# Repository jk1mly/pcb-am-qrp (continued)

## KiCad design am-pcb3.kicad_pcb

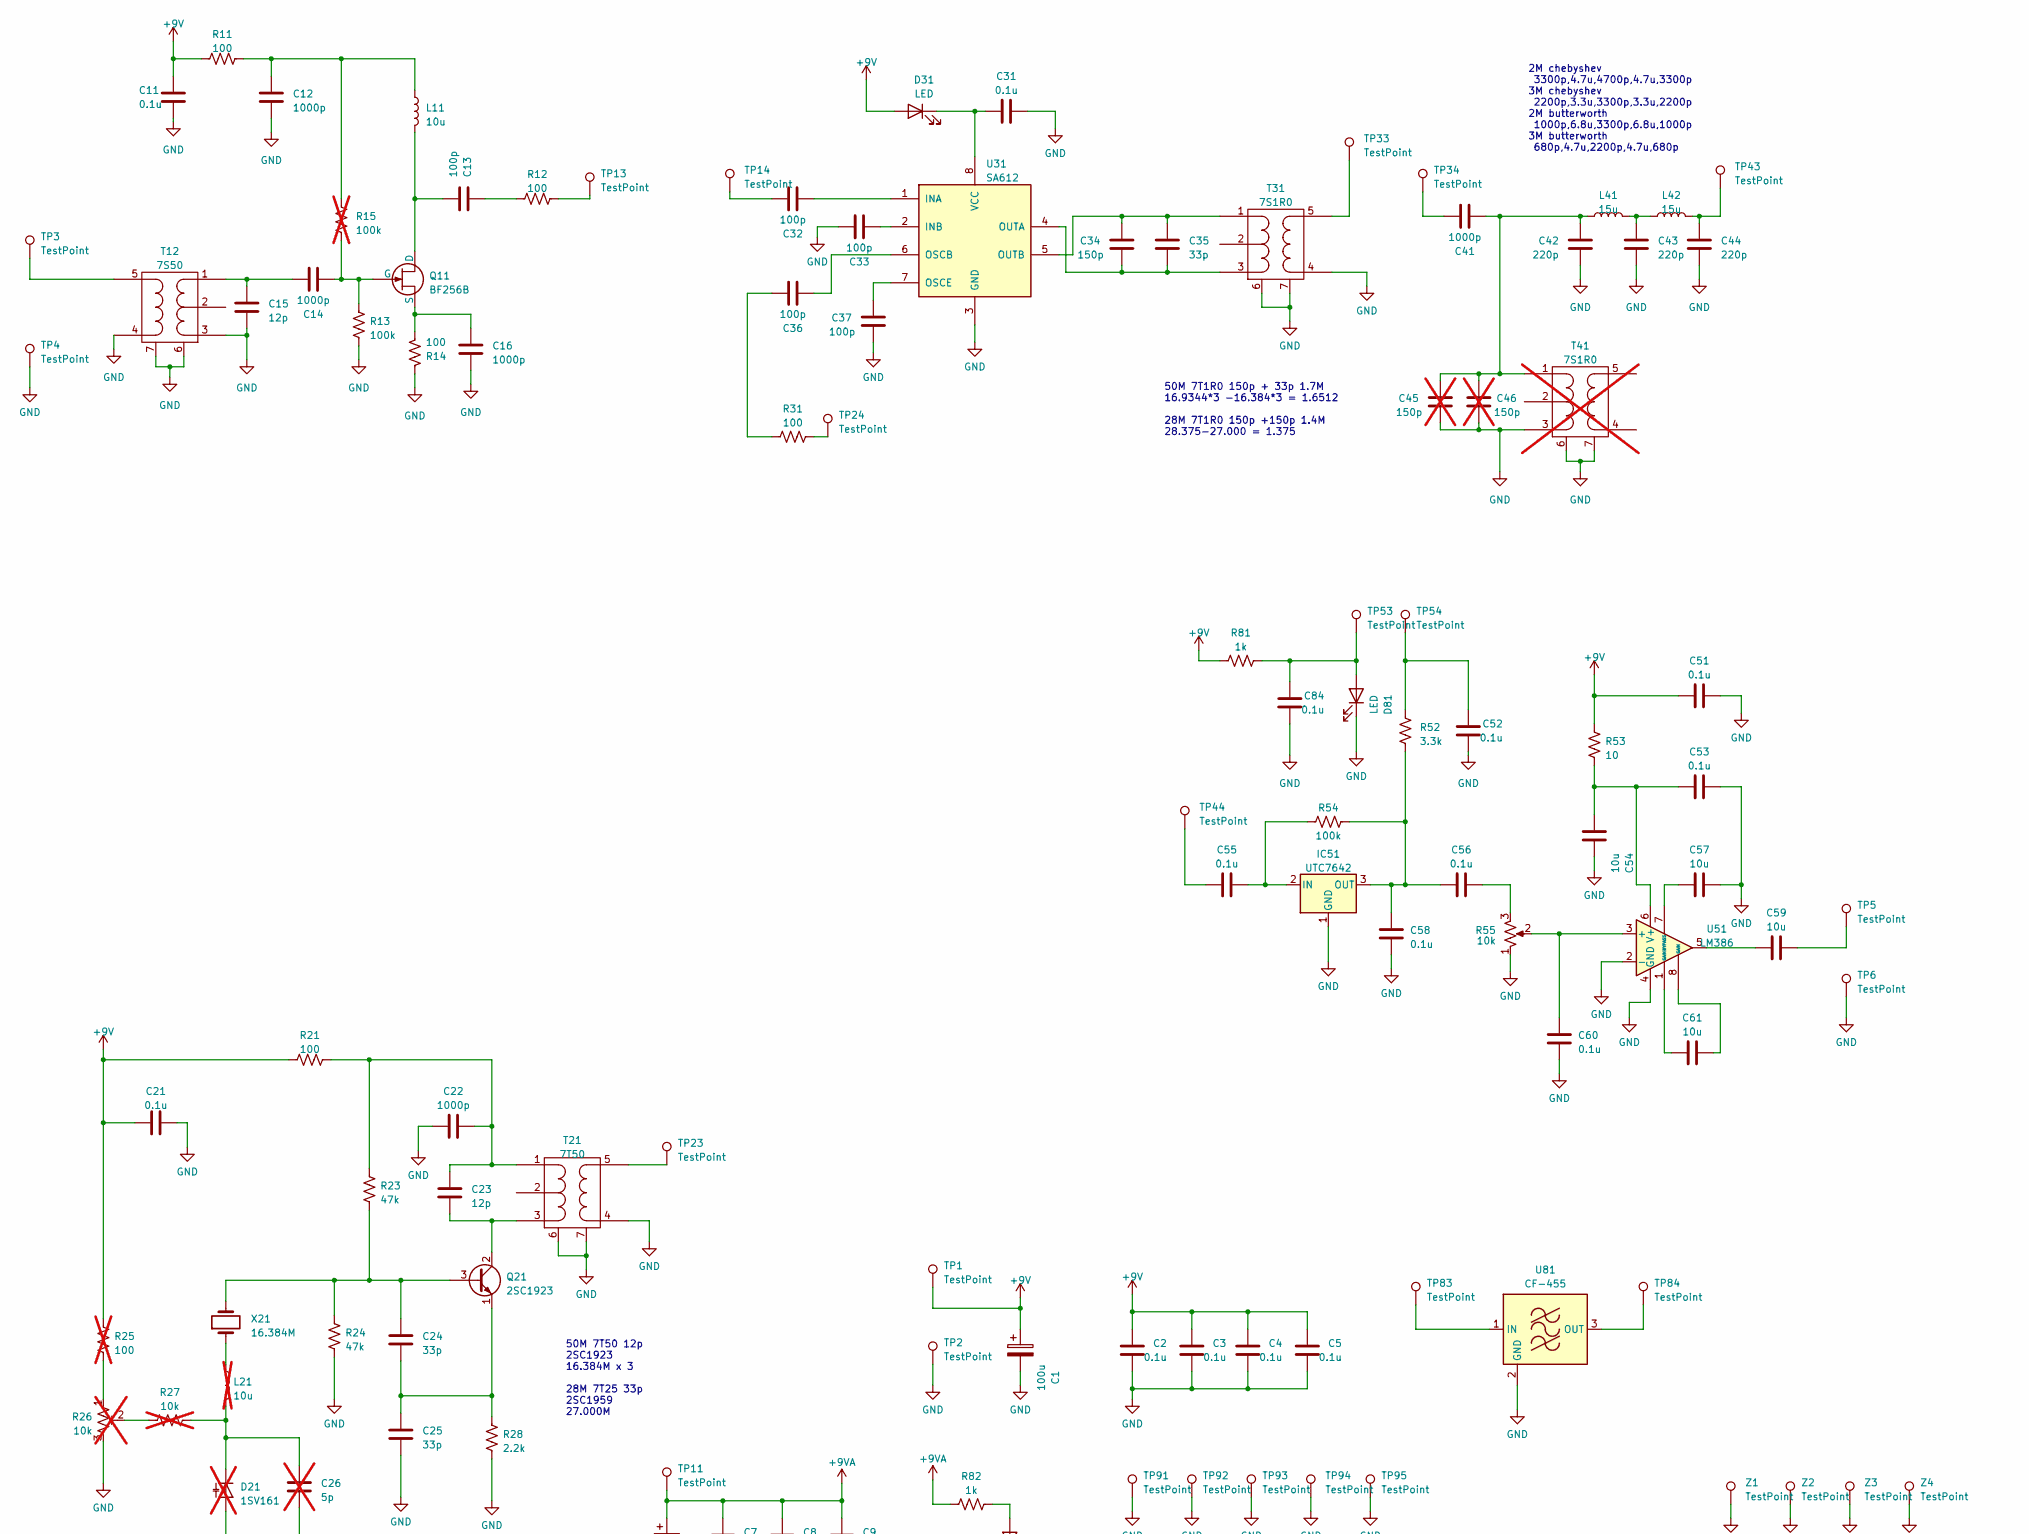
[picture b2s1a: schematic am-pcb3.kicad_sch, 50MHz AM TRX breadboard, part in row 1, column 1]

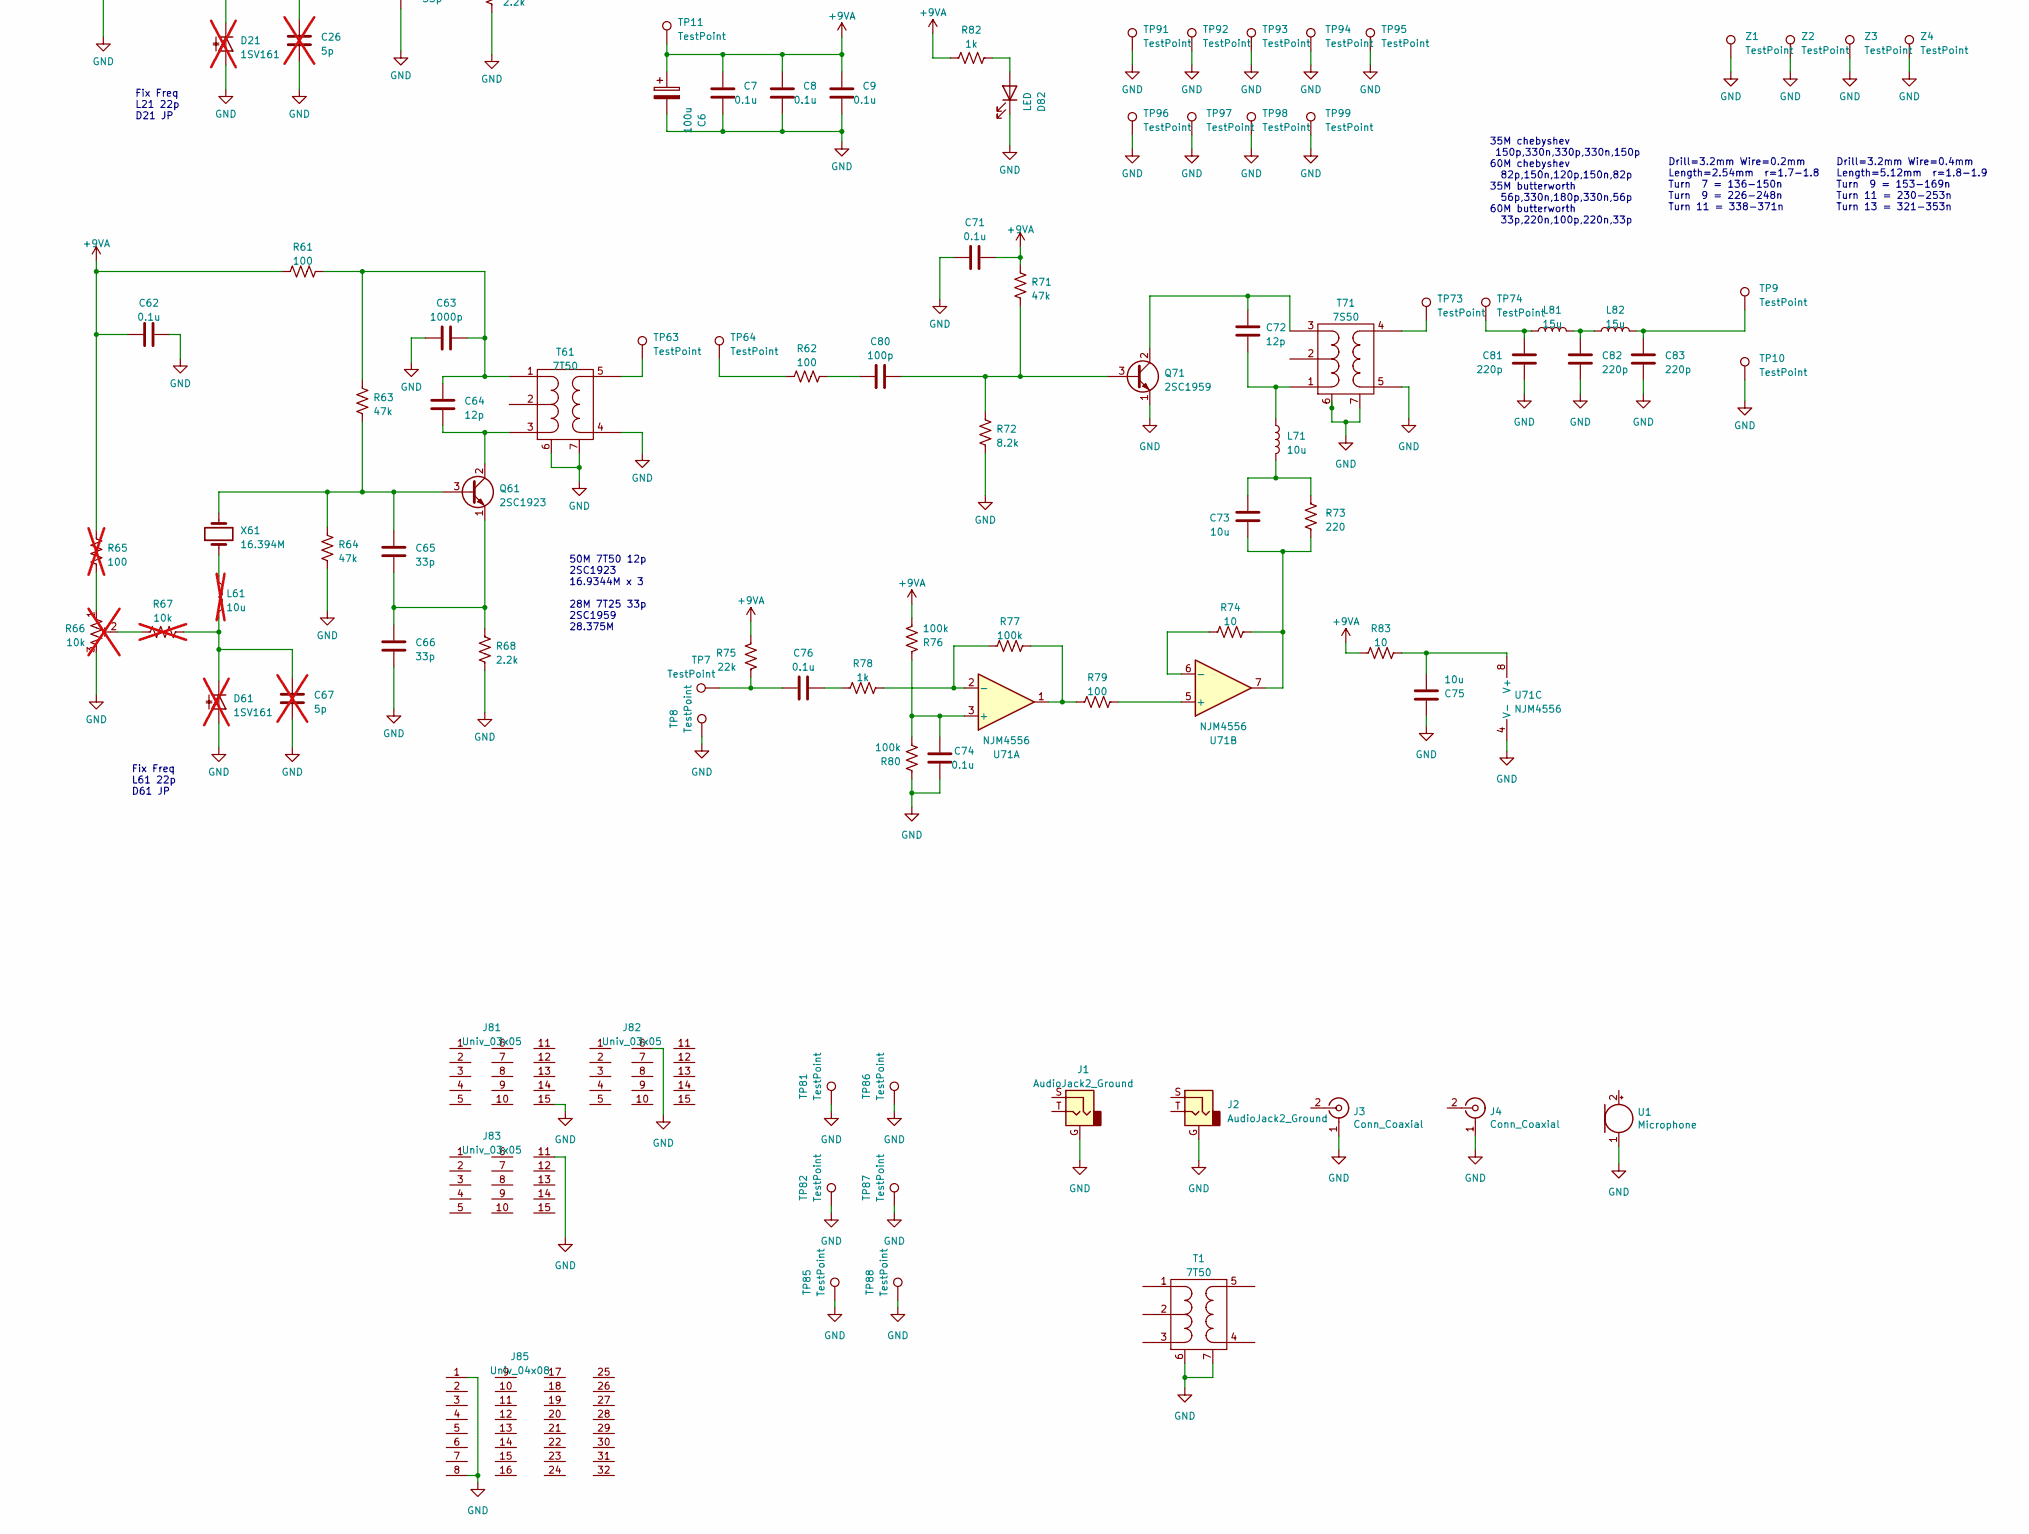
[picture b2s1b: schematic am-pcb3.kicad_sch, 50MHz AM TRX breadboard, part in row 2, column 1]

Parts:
C1, C6: 100u; CP_Radial_D7.5mm_P2.54mm_dot
C2, C3, C4, C5, C7, C8, C9, C11, C21, C31, C51, C52, C53, C55, C56, C58, C60, C62, C71, C74, C76, C84: 0.1u; C_Disc_P2.54mm
C12, C14, C16, C22, C41, C63: 1000p; C_Disc_P2.54mm
C13, C32, C33, C36, C37, C80: 100p; C_Disc_P2.54mm
C15, C23, C64, C72: 12p; C_Disc_P2.54mm
C24, C25, C35, C65, C66: 33p; C_Disc_P2.54mm
C26, C67: 5p; C_Disc_P2.54mm; not fitted
C34: 150p; C_Disc_P2.54mm
C42, C43, C44, C81, C82, C83: 220p; C_Disc_P2.54mm
C45, C46: 150p; C_Disc_P2.54mm; not fitted
C54, C57, C59, C61, C73, C75: 10u; C_Disc_P5.12mm
D21, D61: 1SV161; D_T-1_P5.08mm_Horizontal; not fitted
D31, D81, D82: LED; LED_D3.0mm
IC51: UTC7642; TO-92_Inline_Wide
J1, J2: AudioJack2_Ground; Jack_3.5mm_CUI_SJ1-3525N_Horizontal
J3, J4: Conn_Coaxial; RF_SMA_Vertical_5-1814832-1
J81, J82, J83: Univ_03x05; univ_03x05
J85: Univ_04x08; univ_04x08
L11, L71: 10u; R_Axial_DIN0207_L6.3mm_D2.2mm_P2.54mm_Vertical
L21, L61: 10u; R_Axial_DIN0207_L6.3mm_D2.2mm_P2.54mm_Vertical; not fitted
L41, L42, L81, L82: 15u; R_Axial_DIN0207_L6.3mm_D2.2mm_P2.54mm_Vertical
Q11: BF256B; TO-92_Inline_Wide
Q21, Q61: 2SC1923; TO-92_Inline_Wide
Q71: 2SC1959; TO-92_Inline_Wide
R11, R12, R14, R21, R31, R61, R62, R79: 100; R_Axial_DIN0207_L6.3mm_D2.2mm_P2.54mm_Vertical
R13, R54, R76, R77, R80: 100k; R_Axial_DIN0207_L6.3mm_D2.2mm_P2.54mm_Vertical
R15: 100k; R_Axial_DIN0207_L6.3mm_D2.2mm_P2.54mm_Vertical; not fitted
R23, R24, R63, R64, R71: 47k; R_Axial_DIN0207_L6.3mm_D2.2mm_P2.54mm_Vertical
R25, R65: 100; R_Axial_DIN0207_L6.3mm_D2.2mm_P2.54mm_Vertical; not fitted
R26, R66: 10k; Potentiometer_1; not fitted
R27, R67: 10k; R_Axial_DIN0207_L6.3mm_D2.2mm_P2.54mm_Vertical; not fitted
R28, R68: 2.2k; R_Axial_DIN0207_L6.3mm_D2.2mm_P2.54mm_Vertical
R52: 3.3k; R_Axial_DIN0207_L6.3mm_D2.2mm_P2.54mm_Vertical
R53, R74, R83: 10; R_Axial_DIN0207_L6.3mm_D2.2mm_P2.54mm_Vertical
R55: 10k; Potentiometer_1
R72: 8.2k; R_Axial_DIN0207_L6.3mm_D2.2mm_P2.54mm_Vertical
R73: 220; R_Axial_DIN0207_L6.3mm_D2.2mm_P2.54mm_Vertical
R75: 22k; R_Axial_DIN0207_L6.3mm_D2.2mm_P2.54mm_Vertical
R78, R81, R82: 1k; R_Axial_DIN0207_L6.3mm_D2.2mm_P2.54mm_Vertical
T1, T21, T61: 7T50; coil_7mm
T12, T71: 7S50; coil_7mm
T31: 7S1R0; coil_7mm
T41: 7S1R0; coil_7mm; not fitted
TP1, TP2, TP3, TP4, TP5, TP6, TP7, TP8, TP9, TP10, TP11, TP13, TP14, TP23, TP24, TP33, TP34, TP43, TP44, TP53, TP54, TP63, TP64, TP73, TP74, TP81, TP82, TP83, TP84, TP85, TP86, TP87, TP88, TP91, TP92, TP93, TP94, TP95, TP96, TP97, TP98, TP99: TestPoint; TestPoint_Loop_D2.50mm_Drill1.0mm
U1: Microphone; Mic_CMA-4544PF-W
U31: SA612; DIP-8_W7.62mm_Socket
U51: LM386; DIP-8_W7.62mm_Socket
U71: NJM4556; DIP-8_W7.62mm_Socket
U81: CF-455; CF-3P
X21: 16.384M; Crystal_HC49-U_Vertical
X61: 16.394M; Crystal_HC49-U_Vertical
Z1, Z2, Z3, Z4: TestPoint; TestPoint_Drill3mm

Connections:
+9V: C1.1, C2.1, C3.1, C4.1, C5.1, C11.1, C21.1, C51.1, D31.2 (A), R11.1, R21.1, R25.1, R53.1, R81.1, TP1.1
+9VA: C6.1, C7.1, C8.1, C9.1, C62.1, C71.2, R61.1, R65.1, R71.1, R75.1, R76.2, R82.1, R83.1, TP11.1
GND: C1.2, C2.2, C3.2, C4.2, C5.2, C6.2, C7.2, C8.2, C9.2, C11.2, C12.2, C15.2, C16.2, C21.2, C22.1, C25.2, C26.2, C31.2, C33.1, C37.2, C42.2, C43.2, C44.2, C45.2, C46.2, C51.2, C52.2, C53.2, C54.2, C57.2, C58.1, C60.1, C62.2, C63.1, C66.2, C67.2, C71.1, C74.2, C75.2, C81.2, C82.2, C83.2, C84.2, D21.2 (A), D61.2 (A), D81.1 (K), D82.1 (K), IC51.1 (GND), J1.G, J2.G, J3.1 (G), J4.1 (G), J81.15, J82.6, J83.11, J85.1, J85.8, Q71.1 (E), R13.2, R14.1, R24.1, R26.3, R28.1, R55.1, R64.1, R66.3, R68.1, R72.1, R80.1, T1.6 (G1), T1.7 (G2), T12.3 (PR2), T12.4 (S1), T12.6 (G1), T12.7 (G2), T21.4 (S1), T21.6 (G1), T21.7 (G2), T31.4 (S1), T31.6 (G1), T31.7 (G2), T41.3 (PR2), T41.6 (G1), T41.7 (G2), T61.4 (S1), T61.6 (G1), T61.7 (G2), T71.5 (S1), T71.6 (G1), T71.7 (G2), TP2.1, TP4.1, TP6.1, TP8.1, TP10.1, TP81.1, TP82.1, TP85.1, TP86.1, TP87.1, TP88.1, TP91.1, TP92.1, TP93.1, TP94.1, TP95.1, TP96.1, TP97.1, TP98.1, TP99.1, U1.1 (-), U31.3 (GND), U51.2 (-), U51.4 (GND), U71.4 (V-), U81.2 (GND), Z1.1, Z2.1, Z3.1, Z4.1
unnamed: C12.1, L11.1, R11.2, R15.1
unnamed: C13.1, R12.1
unnamed: C32.1, TP14.1
unnamed: C36.1, R31.1
unnamed: C41.1, TP34.1
unnamed: C43.1, L41.2, L42.1
unnamed: C44.1, L42.2, TP43.1
unnamed: C52.1, R52.1, TP54.1
unnamed: C55.1, TP44.1
unnamed: C56.2, R55.3
unnamed: C59.1, U51.5
unnamed: C59.2, TP5.1
unnamed: C61.1, U51.1 (GAIN)
unnamed: C61.2, U51.8 (GAIN)
unnamed: C73.1, R73.2, R74.2, U71.7
unnamed: C73.2, L71.2, R73.1
unnamed: C76.1, R75.2, TP7.1
unnamed: C76.2, R78.1
unnamed: C80.1, R62.2
unnamed: C81.1, L81.1, TP74.1
unnamed: C82.1, L81.2, L82.1
unnamed: C83.1, L82.2, TP9.1
unnamed: C26.1, D21.1 (K), L21.2, R27.2
unnamed: C31.1, D31.1 (K), U31.8 (VCC)
unnamed: C67.1, D61.1 (K), L61.2, R67.2
unnamed: C84.1, D81.2 (A), R81.2, TP53.1
unnamed: D82.2 (A), R82.2
unnamed: C55.2, IC51.2 (IN), R54.2
unnamed: C56.1, C58.2, IC51.3 (OUT), R52.2, R54.1
unnamed: L21.1, X21.1
unnamed: L61.1, X61.1
unnamed: C13.2, L11.2, Q11.3 (D)
unnamed: C14.2, Q11.1 (G), R13.1, R15.2
unnamed: C16.1, Q11.2 (S), R14.2
unnamed: C24.1, Q21.3 (B), R23.2, R24.2, X21.2
unnamed: C23.2, Q21.2 (C), T21.3 (PR2)
unnamed: C24.2, C25.1, Q21.1 (E), R28.2
unnamed: C65.1, Q61.3 (B), R63.2, R64.2, X61.2
unnamed: C64.2, Q61.2 (C), T61.3 (PR2)
unnamed: C65.2, C66.1, Q61.1 (E), R68.2
unnamed: C80.2, Q71.3 (B), R71.2, R72.2
unnamed: C72.1, Q71.2 (C), T71.3 (PR1)
unnamed: R12.2, TP13.1
unnamed: R25.2, R26.1
unnamed: R26.2, R27.1
unnamed: R31.2, TP24.1
unnamed: R62.1, TP64.1
unnamed: R65.2, R66.1
unnamed: R66.2, R67.1
unnamed: R77.2, R79.1, U71.1
unnamed: C14.1, C15.1, T12.1 (PR1)
unnamed: T12.5 (S2), TP3.1
unnamed: C22.2, C23.1, R21.2, R23.1, T21.1 (PR1)
unnamed: T21.5 (S2), TP23.1
unnamed: C34.1, C35.1, T31.1 (PR1), U31.5 (OUTB)
unnamed: C34.2, C35.2, T31.3 (PR2), U31.4 (OUTA)
unnamed: T31.5 (S2), TP33.1
unnamed: C41.2, C42.1, C45.1, C46.1, L41.1, T41.1 (PR1)
unnamed: C63.2, C64.1, R61.2, R63.1, T61.1 (PR1)
unnamed: T61.5 (S2), TP63.1
unnamed: C72.2, L71.1, T71.1 (PR2)
unnamed: T71.4 (S2), TP73.1
unnamed: C32.2, U31.1 (INA)
unnamed: C33.2, U31.2 (INB)
unnamed: C36.2, U31.6 (OSCB)
unnamed: C37.1, U31.7 (OSCE)
unnamed: C60.2, R55.2, U51.3 (+)
unnamed: C57.1, U51.7 (BYPASS)
unnamed: C53.1, C54.1, R53.2, U51.6 (V+)
unnamed: C74.1, R76.1, R80.2, U71.3 (+)
unnamed: R77.1, R78.2, U71.2 (-)
unnamed: R79.2, U71.5 (+)
unnamed: R74.1, U71.6 (-)
unnamed: C75.1, R83.2, U71.8 (V+)
unnamed: TP83.1, U81.1 (IN)
unnamed: TP84.1, U81.3 (OUT)

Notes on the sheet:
50M 7T1R0 150p + 33p 1.7M 16.9344*3 -16.384*3 = 1.6512 28M 7T1R0 150p +150p 1.4M 28.375-27.000 = 1.375
Drill=3.2mm Wire=0.4mm Length=5.12mm r=1.8-1.9 Turn 9 = 153-169n Turn 11 = 230-253n Turn 13 = 321-353n
2M chebyshev 3300p,4.7u,4700p,4.7u,3300p 3M chebyshev 2200p,3.3u,3300p,3.3u,2200p 2M butterworth 1000p,6.8u,3300p,6.8u,1000p 3M butterworth 680p,4.7u,2200p,4.7u,680p
Fix Freq L61 22p D61 JP
Drill=3.2mm Wire=0.2mm Length=2.54mm r=1.7-1.8 Turn 7 = 136-150n Turn 9 = 226-248n Turn 11 = 338-371n
50M 7T50 12p 2SC1923 16.9344M x 3 28M 7T25 33p 2SC1959 28.375M
35M chebyshev 150p,330n,330p,330n,150p 60M chebyshev 82p,150n,120p,150n,82p 35M butterworth 56p,330n,180p,330n,56p 60M butterworth 33p,220n,100p,220n,33p
50M 7T50 12p 2SC1923 16.384M x 3 28M 7T25 33p 2SC1959 27.000M
Fix Freq L21 22p D21 JP

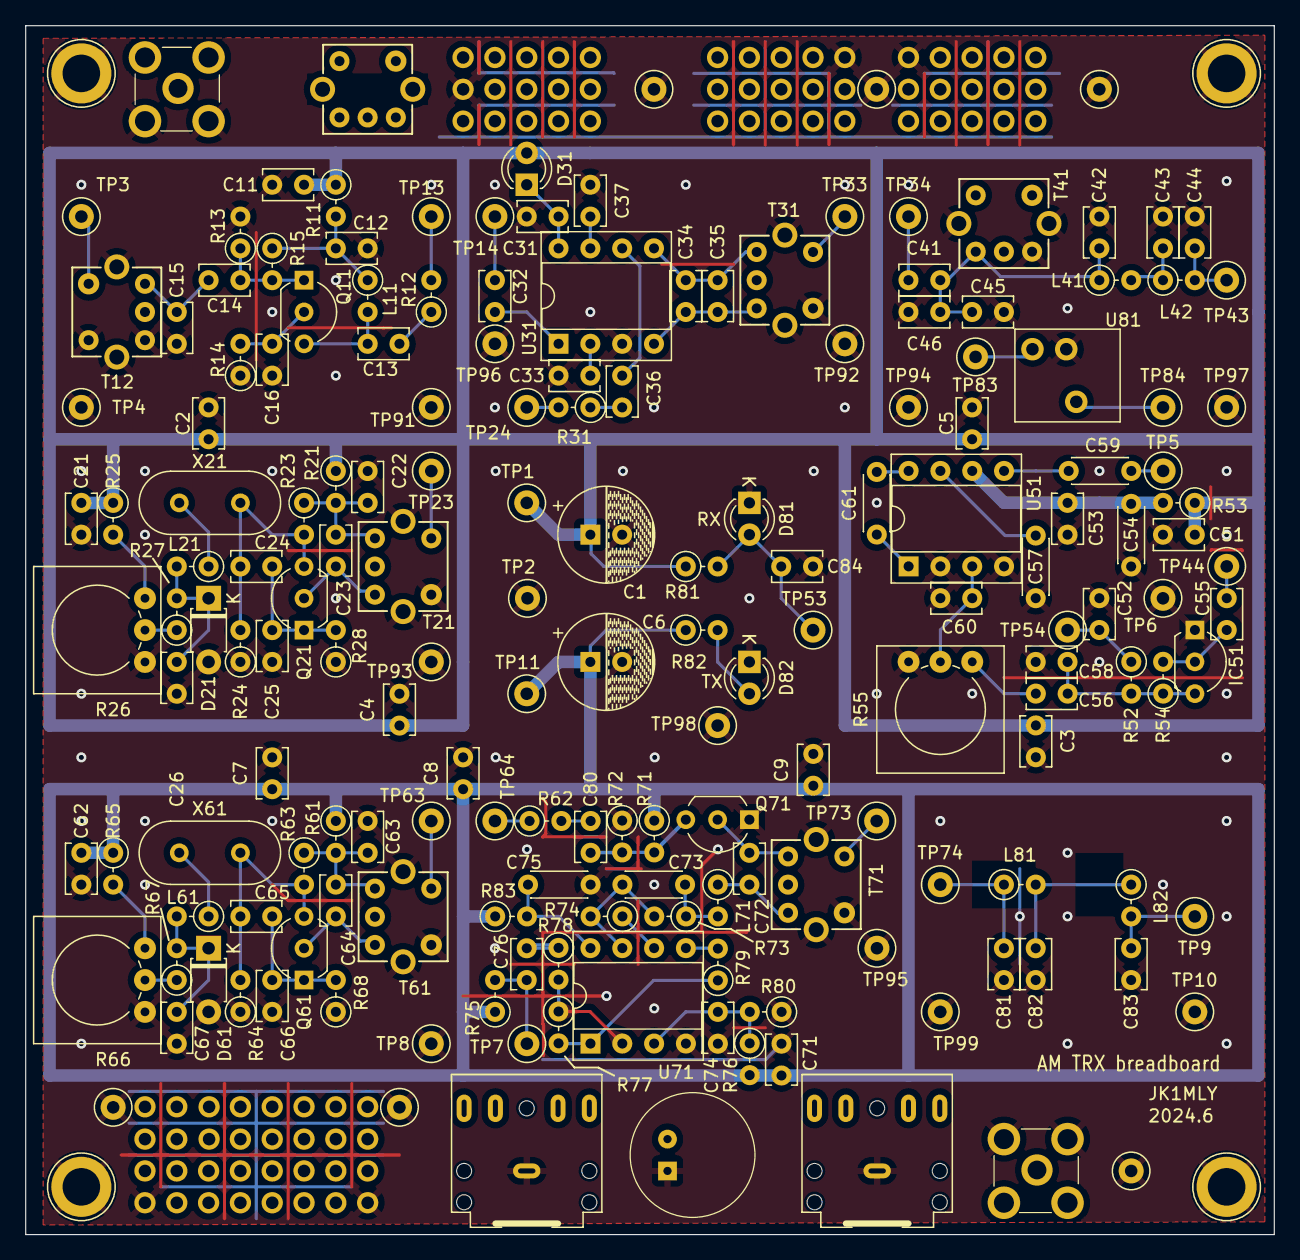
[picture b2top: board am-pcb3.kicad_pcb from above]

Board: 2 copper layers, 99.7 x 96.5 mm, 186 parts (0 on the bottom side), 79 nets.

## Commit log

2024-07-13 Add files via upload
    KiCadデータを登録
2024-07-13 Add files via upload
    pcb3は受信ミキサをSA602に変更 変調回路のドライブをNJM4556に変更
